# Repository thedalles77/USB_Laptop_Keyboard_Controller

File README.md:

# USB_Laptop_Keyboard_Controller
 This repo contains all the files that are needed to make a USB keyboard/touchpad controller as well as a KVM from an old laptop.

 See the USB keyboard video at https://vimeo.com/458595950 and the updated video at https://vimeo.com/888367797?share=copy
 
 See the keyboard Instructable at https://www.instructables.com/id/How-to-Make-a-USB-Laptop-Keyboard-Controller/

 Instead of the manual method to create the key matrix, use Marcel's Python program which I've forked and updated so it will work with the Teensy 4.0, 4.1, and 2.0++. 
 
 The updated Python code is here:
 
 https://github.com/thedalles77/USB_Laptop_Keyboard_Controller-1/blob/master/matrixgenerator.py
 
 See the KVM Instructable at https://www.instructables.com/DIY-Portable-KVM-Crashcart-From-Recycled-Laptop-Pr/ 

 If you don't know how to solder but still want to build a USB laptop keyboard, check out the "No_solder_method" PDF file at https://github.com/thedalles77/USB_Laptop_Keyboard_Controller/blob/master/Keyboard_Scanner_Eagle_Layouts/No_solder_method.pdf.

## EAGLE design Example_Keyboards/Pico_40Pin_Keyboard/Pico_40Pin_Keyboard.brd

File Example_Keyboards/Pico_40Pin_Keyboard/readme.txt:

This project is in development.

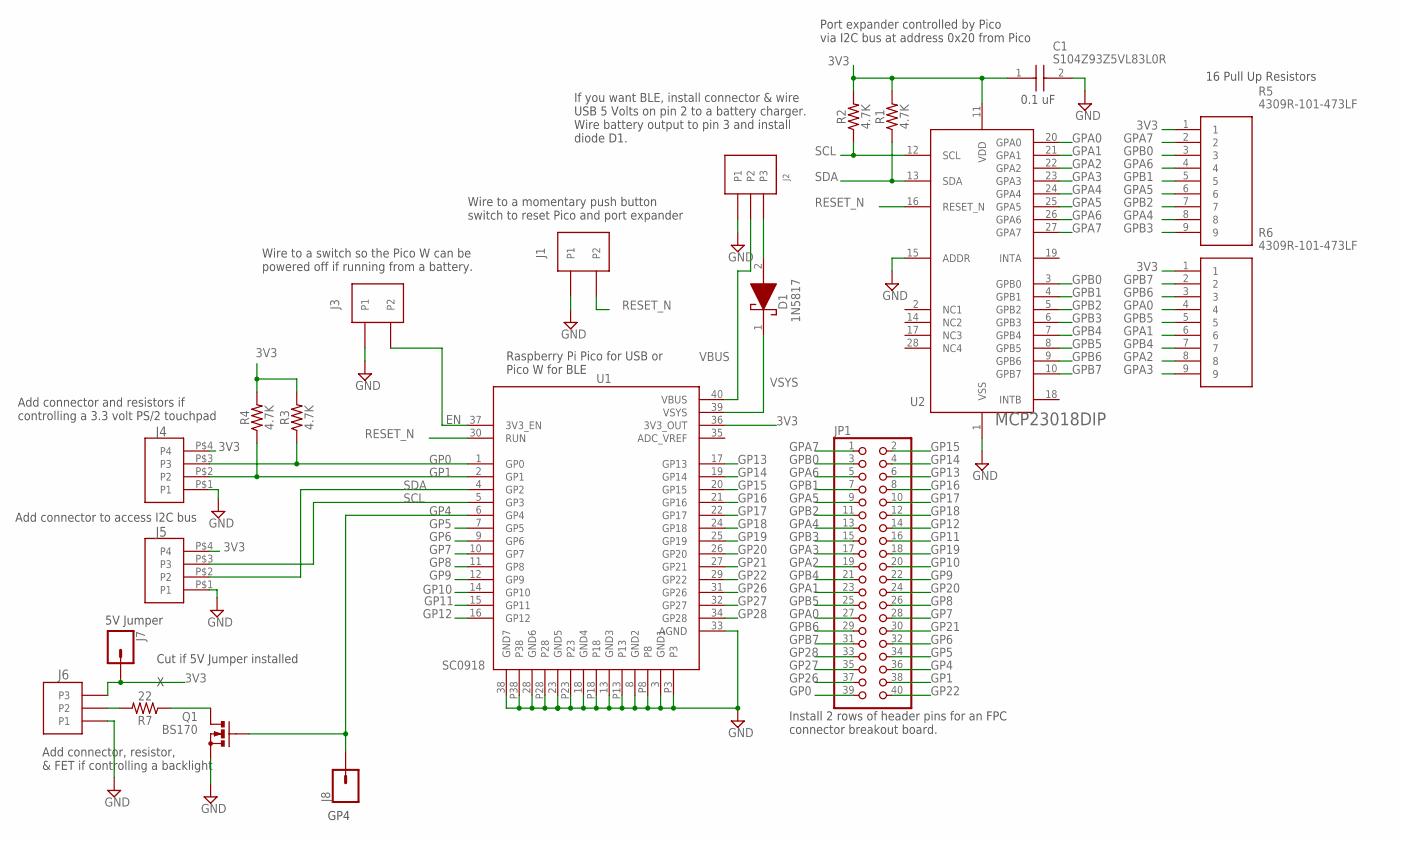
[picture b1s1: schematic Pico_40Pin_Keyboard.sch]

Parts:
C1: S104Z93Z5VL83L0R
D1: 1N5817; DIOAD1410W86L470D235
J1, J3: JST-PH-2PIN
J2, J6: JST-PH-3PIN
J4, J5: JST-PH-4PIN
J7, J8: CONN_01; 1X01
JP1: PINHD-2X20; 2X20
Q1: BS170; SOT54E
R1, R2, R3, R4: 4.7K; AXIAL-0.3
R5, R6: 4309R-101-473LF
R7: 22; AXIAL-0.3
U1: SC0918; MODULE_SC0918
U2: MCP23018DIP

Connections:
3V3: C1.1, J4.P$4 (P4), J5.P$4 (P4), J6.P$3 (P3), J7.1, R1.P$2 (2), R2.P$2 (2), R3.P$2 (2), R4.P$2 (2), R5.1, R6.1, U1.36 (3V3_OUT), U2.11 (VDD)
ADC_VREF: U1.35 (ADC_VREF)
EN: J3.P$2 (P2), U1.37 (3V3_EN)
GND: C1.2, J1.P$1 (P1), J2.P$1 (P1), J3.P$1 (P1), J4.P$1 (P1), J5.P$1 (P1), J6.P$1 (P1), Q1.S, U1.3 (GND1), U1.8 (GND2), U1.13 (GND3), U1.18 (GND4), U1.23 (GND5), U1.28 (GND6), U1.33 (AGND), U1.38 (GND7), U1.P3, U1.P8, U1.P13, U1.P18, U1.P23, U1.P28, U1.P38, U2.1 (VSS), U2.15 (ADDR)
GP0: J4.P$3 (P3), JP1.39, R3.P$1 (1), U1.1 (GP0)
GP1: J4.P$2 (P2), JP1.38, R4.P$1 (1), U1.2 (GP1)
GP4: J8.1, JP1.36, Q1.G, U1.6 (GP4)
GP5: JP1.34, U1.7 (GP5)
GP6: JP1.32, U1.9 (GP6)
GP7: JP1.28, U1.10 (GP7)
GP8: JP1.26, U1.11 (GP8)
GP9: JP1.22, U1.12 (GP9)
GP10: JP1.20, U1.14 (GP10)
GP11: JP1.16, U1.15 (GP11)
GP12: JP1.14, U1.16 (GP12)
GP13: JP1.6, U1.17 (GP13)
GP14: JP1.4, U1.19 (GP14)
GP15: JP1.2, U1.20 (GP15)
GP16: JP1.8, U1.21 (GP16)
GP17: JP1.10, U1.22 (GP17)
GP18: JP1.12, U1.24 (GP18)
GP19: JP1.18, U1.25 (GP19)
GP20: JP1.24, U1.26 (GP20)
GP21: JP1.30, U1.27 (GP21)
GP22: JP1.40, U1.29 (GP22)
GP26: JP1.37, U1.31 (GP26)
GP27: JP1.35, U1.32 (GP27)
GP28: JP1.33, U1.34 (GP28)
GPA0: JP1.27, R6.4, U2.20 (GPA0)
GPA1: JP1.23, R6.6, U2.21 (GPA1)
GPA2: JP1.19, R6.8, U2.22 (GPA2)
GPA3: JP1.17, R6.9, U2.23 (GPA3)
GPA4: JP1.13, R5.8, U2.24 (GPA4)
GPA5: JP1.9, R5.6, U2.25 (GPA5)
GPA6: JP1.5, R5.4, U2.26 (GPA6)
GPA7: JP1.1, R5.2, U2.27 (GPA7)
GPB0: JP1.3, R5.3, U2.3 (GPB0)
GPB1: JP1.7, R5.5, U2.4 (GPB1)
GPB2: JP1.11, R5.7, U2.5 (GPB2)
GPB3: JP1.15, R5.9, U2.6 (GPB3)
GPB4: JP1.21, R6.7, U2.7 (GPB4)
GPB5: JP1.25, R6.5, U2.8 (GPB5)
GPB6: JP1.29, R6.3, U2.9 (GPB6)
GPB7: JP1.31, R6.2, U2.10 (GPB7)
unnamed: J6.P$2 (P2), R7.P$2 (2)
unnamed: Q1.D, R7.P$1 (1)
RESET_N: J1.P$2 (P2), U1.30 (RUN), U2.16 (RESET_N)
SCL: J5.P$3 (P3), R2.P$1 (1), U1.5 (GP3), U2.12 (SCL)
SDA: J5.P$2 (P2), R1.P$1 (1), U1.4 (GP2), U2.13 (SDA)
VBAT: D1.2 (A), J2.P$3 (P3)
VBUS: J2.P$2 (P2), U1.40 (VBUS)
VSYS: D1.1 (K), U1.39 (VSYS)

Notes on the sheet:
If you want BLE, install connector & wire USB 5 Volts on pin 2 to a battery charger. Wire battery output to pin 3 and install diode D1.
Wire to a momentary push button switch to reset Pico and port expander
Wire to a switch so the Pico W can be powered off if running from a battery.
Install 2 rows of header pins for an FPC connector breakout board.
0.1 uF
Raspberry Pi Pico for USB or Pico W for BLE
Add connector and resistors if controlling a 3.3 volt PS/2 touchpad
Add connector to access I2C bus
Port expander controlled by Pico via I2C bus at address 0x20 from Pico
16 Pull Up Resistors
Cut if 5V Jumper installed
5V Jumper
GP4
Add connector, resistor, & FET if controlling a backlight

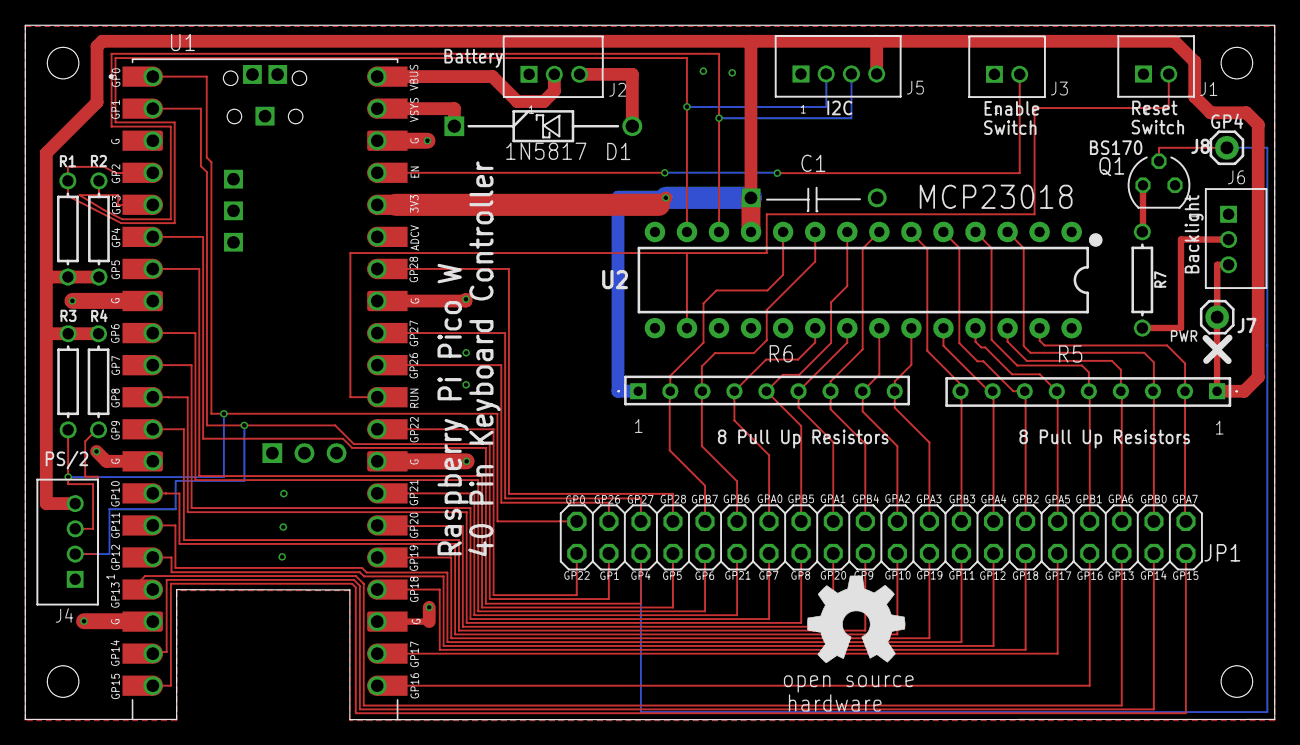
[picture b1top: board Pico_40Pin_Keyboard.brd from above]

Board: 2 copper layers, 99.0 x 55.0 mm, 23 parts (0 on the bottom side), 51 nets.

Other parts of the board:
U$1, U$2: OSHW_8MM

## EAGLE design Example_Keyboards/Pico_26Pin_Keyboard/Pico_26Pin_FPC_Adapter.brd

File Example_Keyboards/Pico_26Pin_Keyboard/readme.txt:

Laptop Keyboard with up to 26 pins on its FPC cable is Controlled with a Raspberry Pi Pico for USB operation.

See the PDF and step 16 of my Instructable for more information

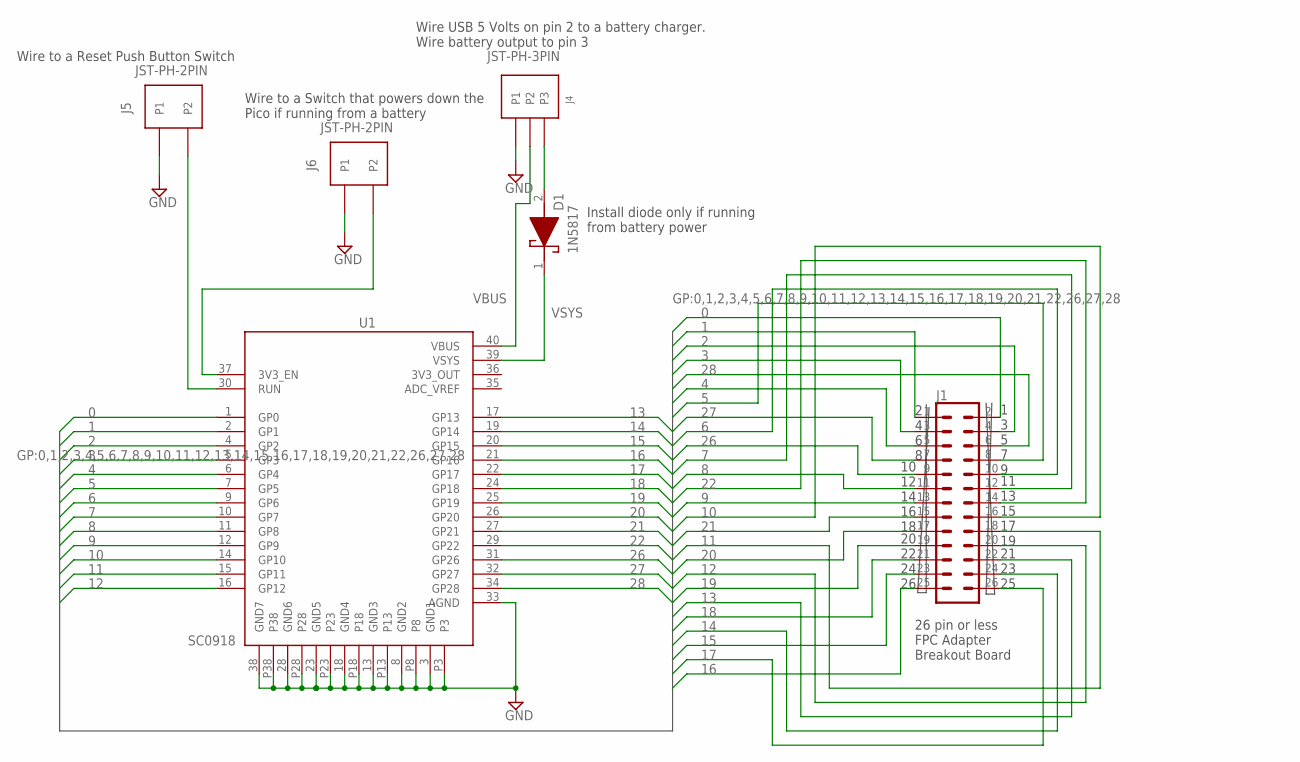
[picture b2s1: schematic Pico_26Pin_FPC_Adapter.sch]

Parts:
D1: 1N5817; DIOAD1410W86L470D235
J1: CONN_13X22X13; 2X13
J4: JST-PH-3PIN
J5, J6: JST-PH-2PIN
U1: SC0918; MODULE_SC0918

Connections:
0: J1.2, U1.1 (GP0)
1: J1.1, U1.2 (GP1)
2: J1.4, U1.4 (GP2)
3: J1.3, U1.5 (GP3)
3V3_OUT: U1.36 (3V3_OUT)
4: J1.5, U1.6 (GP4)
5: J1.8, U1.7 (GP5)
6: J1.10, U1.9 (GP6)
7: J1.12, U1.10 (GP7)
8: J1.11, U1.11 (GP8)
9: J1.13, U1.12 (GP9)
10: J1.16, U1.14 (GP10)
11: J1.18, U1.15 (GP11)
12: J1.20, U1.16 (GP12)
13: J1.22, U1.17 (GP13)
14: J1.24, U1.19 (GP14)
15: J1.23, U1.20 (GP15)
16: J1.25, U1.21 (GP16)
17: J1.26, U1.22 (GP17)
18: J1.21, U1.24 (GP18)
19: J1.19, U1.25 (GP19)
20: J1.17, U1.26 (GP20)
21: J1.15, U1.27 (GP21)
22: J1.14, U1.29 (GP22)
26: J1.9, U1.31 (GP26)
27: J1.7, U1.32 (GP27)
28: J1.6, U1.34 (GP28)
ADC_VREF: U1.35 (ADC_VREF)
GND: J4.P$1 (P1), J5.P$1 (P1), J6.P$1 (P1), U1.3 (GND1), U1.8 (GND2), U1.13 (GND3), U1.18 (GND4), U1.23 (GND5), U1.28 (GND6), U1.33 (AGND), U1.38 (GND7), U1.P3, U1.P8, U1.P13, U1.P18, U1.P23, U1.P28, U1.P38
unnamed: J5.P$2 (P2), U1.30 (RUN)
unnamed: J6.P$2 (P2), U1.37 (3V3_EN)
VBAT: D1.2 (A), J4.P$3 (P3)
VBUS: J4.P$2 (P2), U1.40 (VBUS)
VSYS: D1.1 (K), U1.39 (VSYS)

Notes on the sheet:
Wire USB 5 Volts on pin 2 to a battery charger. Wire battery output to pin 3
Wire to a Reset Push Button Switch
Wire to a Switch that powers down the Pico if running from a battery
Install diode only if running from battery power
26 pin or less FPC Adapter Breakout Board
1 3 5 7 9
11 13 15 17 19
21 23 25
2 4 6 8
10 12 14 16 18
20 22 24 26

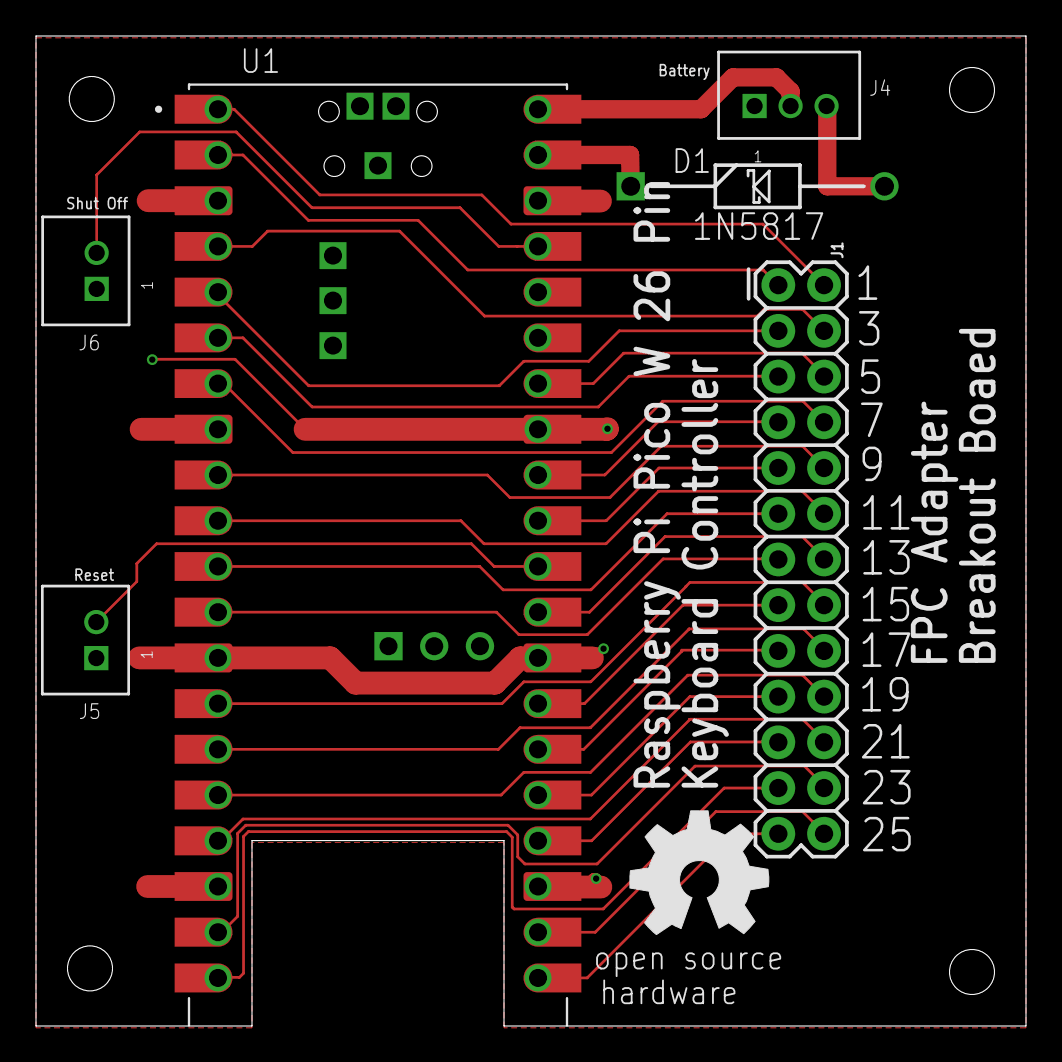
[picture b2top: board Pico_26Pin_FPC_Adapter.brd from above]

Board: 2 copper layers, 55.0 x 55.0 mm, 8 parts (0 on the bottom side), 32 nets.

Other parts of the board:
U$1, U$2: OSHW_8MM

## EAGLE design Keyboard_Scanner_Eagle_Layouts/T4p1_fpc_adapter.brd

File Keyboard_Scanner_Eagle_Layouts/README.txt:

The Eagle .brd files can be sent to OSHPark. The Zipped gerber files can be sent to JLCPCB for fabrication.

The files in this folder are for creating a "generic" FPC connector board. For keyboards with special connectors, look in the Example_Keyboards folder.

If you want to build a prototype keyboard controller without soldering a board, read the PDF file titled "No_solder_method".

The Teensy 4.0, 4.1, and 2.0++ clone are available for purchase.

Teensy 4.0 board, schematic, and zipped Gerber files are called T4p0 and T4p0_cutout. They accept 1mm, 0.8mm, and 0.5mm surface mount FPC connectors.

Teensy 4.1 board, schematic, and zipped Gerber files are called T4p1 and T4p1_cutout. They accept 1mm, 0.8mm, and 0.5mm surface mount FPC connectors.

The T4p1_thruhole board, schematic, and zipped Gerber files are for 1mm or 1.25mm pitch thru hole connectors. 

The Teensy 2.0++ (clone) uses the Keyboard_Scanner_2pp_RevA board, schematic, and zipped Gerber files. This board avoids using the I/O pin tied to the LED. 

The following are useful FPC breakout boards:

FPC_8pin1mm.brd EagleCad file for 8 pin 1mm breakout board

FPC_10pin0p5mm.brd  EagleCad file for 10 pin 0.5mm breakout board

FPC_18pin1mm.brd  EagleCad file for 18 pin 1mm, 0.8mm, or 0.5mm breakout board

The following boards use the Teensy LC and 3.2 which are obsolete and should not be used for new designs. Use the Teensy 4.0, 4.1, and 2.0++ (clone) for new designs.

Keyboard_Scanner.brd EagleCad circuit board file for Teensy LC or 3.2. Original layout shown in the video. The LT2 board is better.

Keyboard_Scanner_LT.brd EagleCad file same as above with 2 bit Level Translator for touchpad Clock and Data on Teensy LC side. The LT2 board is better.

Keyboard_Scanner_LT2.brd EagleCad file same as above with improved hole spacing for using right angle header on Teensy 3.2 backside signals

Keyboard_Scanner_LT_0p5.brd EagleCad file same as above except made for a 0.5mm pitch FPC connector

Keyboard_Scanner_Dual.brd EagleCad file is for keyboards with dual FPC cables but it uses the obsolete Teensy LC and 3.2

Keyboard_Scanner_4p0.brd EagleCad file for Teensy LC or 4.0 with 1mm or 0.8mm pitch. The T4p0.brd is better

Keyboard_Scanner_4p0_0p5.brd EagleCad file for Teensy LC or 4.0 with 1mm or 0.5mm pitch. The T4p0.brd is better

Keyboard_Scanner_LC_thruhole.brd EagleCad file for thru-hole 1mm pitch FPC cables with up to 26 pins. The T4p1_thruhole.brd is better

TeensyLC_1p25.brd EagleCad file for thru-hole 1.25mm pitch FPC cables with up to 26 pins. The T4p1_thruhole.brd is better

Keyboard_Scanner_2pp.brd EagleCad file for Teensy ++2.0. The Keyboard_Scanner_2pp_RevA.brd is better

Teensy3p2Cutout.brd EagleCad file has a cutout for a Teensy 3.2. The T4p0_cutout.brd is better.

Teensy3p2CutoutFlip.brd EagleCad file is the same as above file but it has the cutout on the right side instead of the left side.

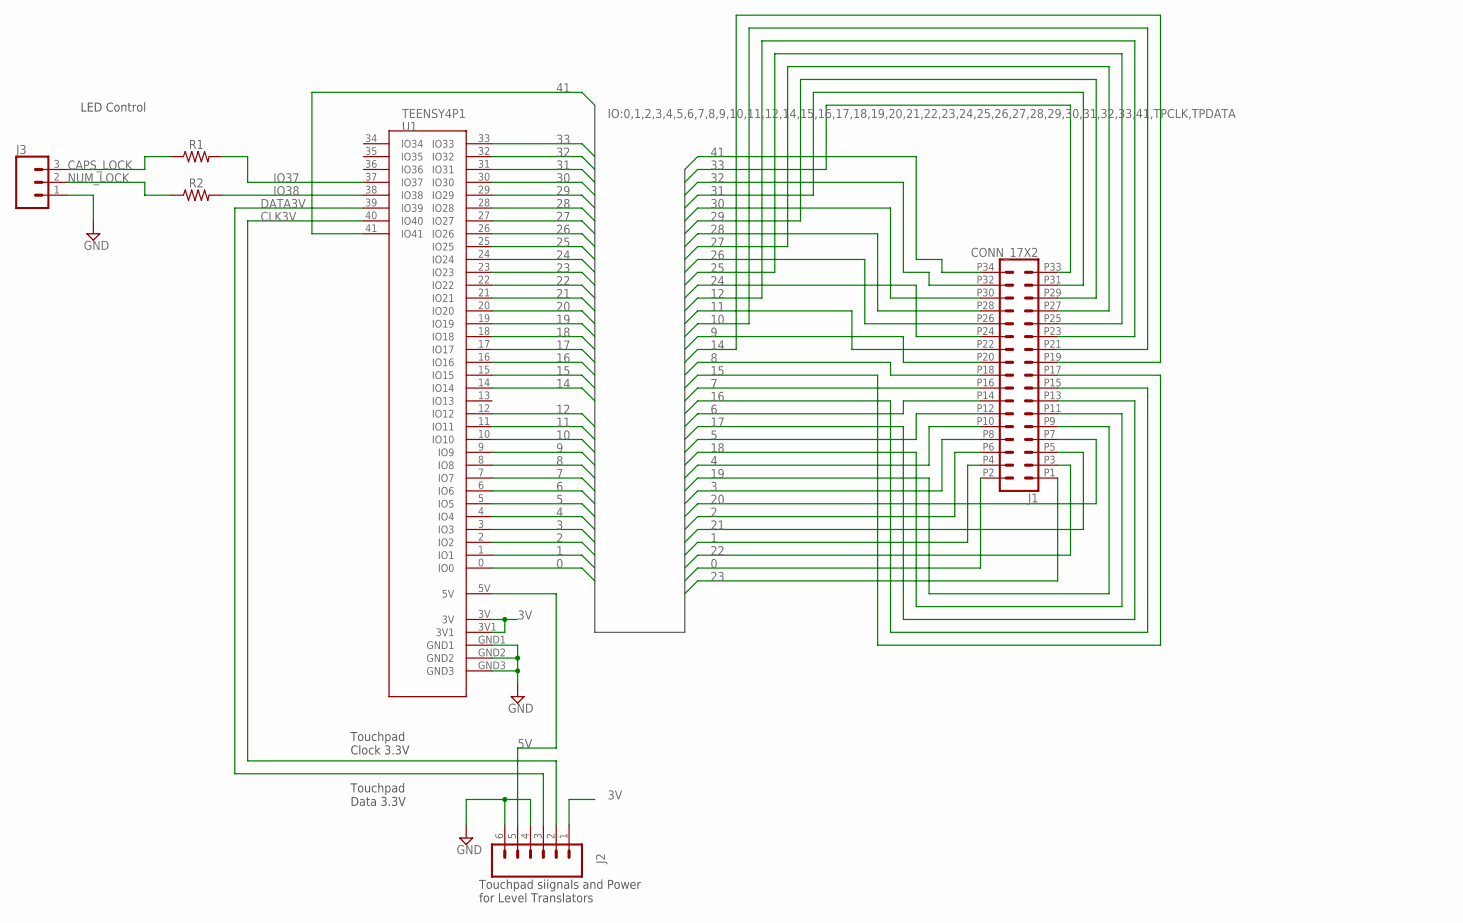
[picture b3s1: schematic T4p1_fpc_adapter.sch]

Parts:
J1: CONN_17X2; 2X17
J2: CONN_06NO_SILK_FEMALE_PTH; 1X06_NO_SILK
J3: CONN_031X03_NO_SILK; 1X03_NO_SILK
R1, R2: RESISTOR_AXIAL; AXIAL-0.3
U1: TEENSY4P1

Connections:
0: J1.P2 (2), U1.0 (IO0)
1: J1.P4 (4), U1.1 (IO1)
2: J1.P6 (6), U1.2 (IO2)
3: J1.P8 (8), U1.3 (IO3)
3V: J2.1, U1.3V, U1.3V1
4: J1.P10 (10), U1.4 (IO4)
5: J1.P12 (12), U1.5 (IO5)
5V: J2.5, U1.5V
6: J1.P14 (14), U1.6 (IO6)
7: J1.P16 (16), U1.7 (IO7)
8: J1.P18 (18), U1.8 (IO8)
9: J1.P20 (20), U1.9 (IO9)
10: J1.P21 (21), U1.10 (IO10)
11: J1.P22 (22), U1.11 (IO11)
12: J1.P23 (23), U1.12 (IO12)
14: J1.P19 (19), U1.14 (IO14)
15: J1.P17 (17), U1.15 (IO15)
16: J1.P15 (15), U1.16 (IO16)
17: J1.P13 (13), U1.17 (IO17)
18: J1.P11 (11), U1.18 (IO18)
19: J1.P9 (9), U1.19 (IO19)
20: J1.P7 (7), U1.20 (IO20)
21: J1.P5 (5), U1.21 (IO21)
22: J1.P3 (3), U1.22 (IO22)
23: J1.P1 (1), U1.23 (IO23)
24: J1.P24 (24), U1.24 (IO24)
25: J1.P25 (25), U1.25 (IO25)
26: J1.P26 (26), U1.26 (IO26)
27: J1.P27 (27), U1.27 (IO27)
28: J1.P28 (28), U1.28 (IO28)
29: J1.P29 (29), U1.29 (IO29)
30: J1.P30 (30), U1.30 (IO30)
31: J1.P31 (31), U1.31 (IO31)
32: J1.P32 (32), U1.32 (IO32)
33: J1.P33 (33), U1.33 (IO33)
41: J1.P34 (34), U1.41 (IO41)
CAPS_LOCK: J3.3, R1.P$1 (1)
CLK3V: J2.2, U1.40 (IO40)
DATA3V: J2.3, U1.39 (IO39)
GND: J2.4, J2.6, J3.1, U1.GND1, U1.GND2, U1.GND3
IO37: R1.P$2 (2), U1.37 (IO37)
IO38: R2.P$2 (2), U1.38 (IO38)
NUM_LOCK: J3.2, R2.P$1 (1)

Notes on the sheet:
Touchpad siignals and Power for Level Translators
Touchpad Clock 3.3V
Touchpad Data 3.3V
LED Control

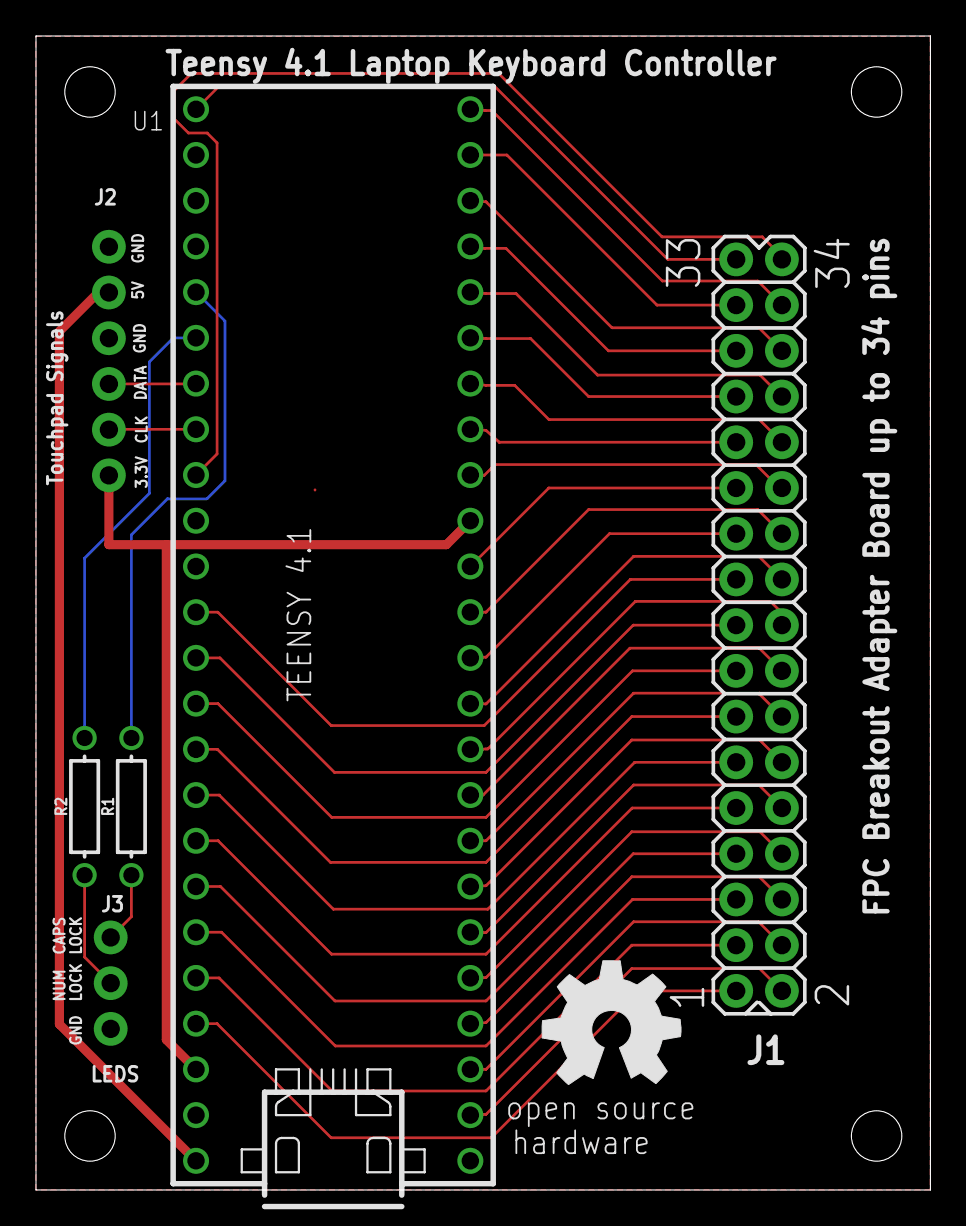
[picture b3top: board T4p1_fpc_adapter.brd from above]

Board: 2 copper layers, 49.7 x 64.1 mm, 8 parts (0 on the bottom side), 43 nets.

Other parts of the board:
U$1, U$2: OSHW_8MM

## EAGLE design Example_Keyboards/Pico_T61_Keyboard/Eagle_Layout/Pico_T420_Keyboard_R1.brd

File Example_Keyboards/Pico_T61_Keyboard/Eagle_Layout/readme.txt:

The ZIP file is the Eagle .BRD file converted to GERBER format for sending to board houses like JLCPCB.

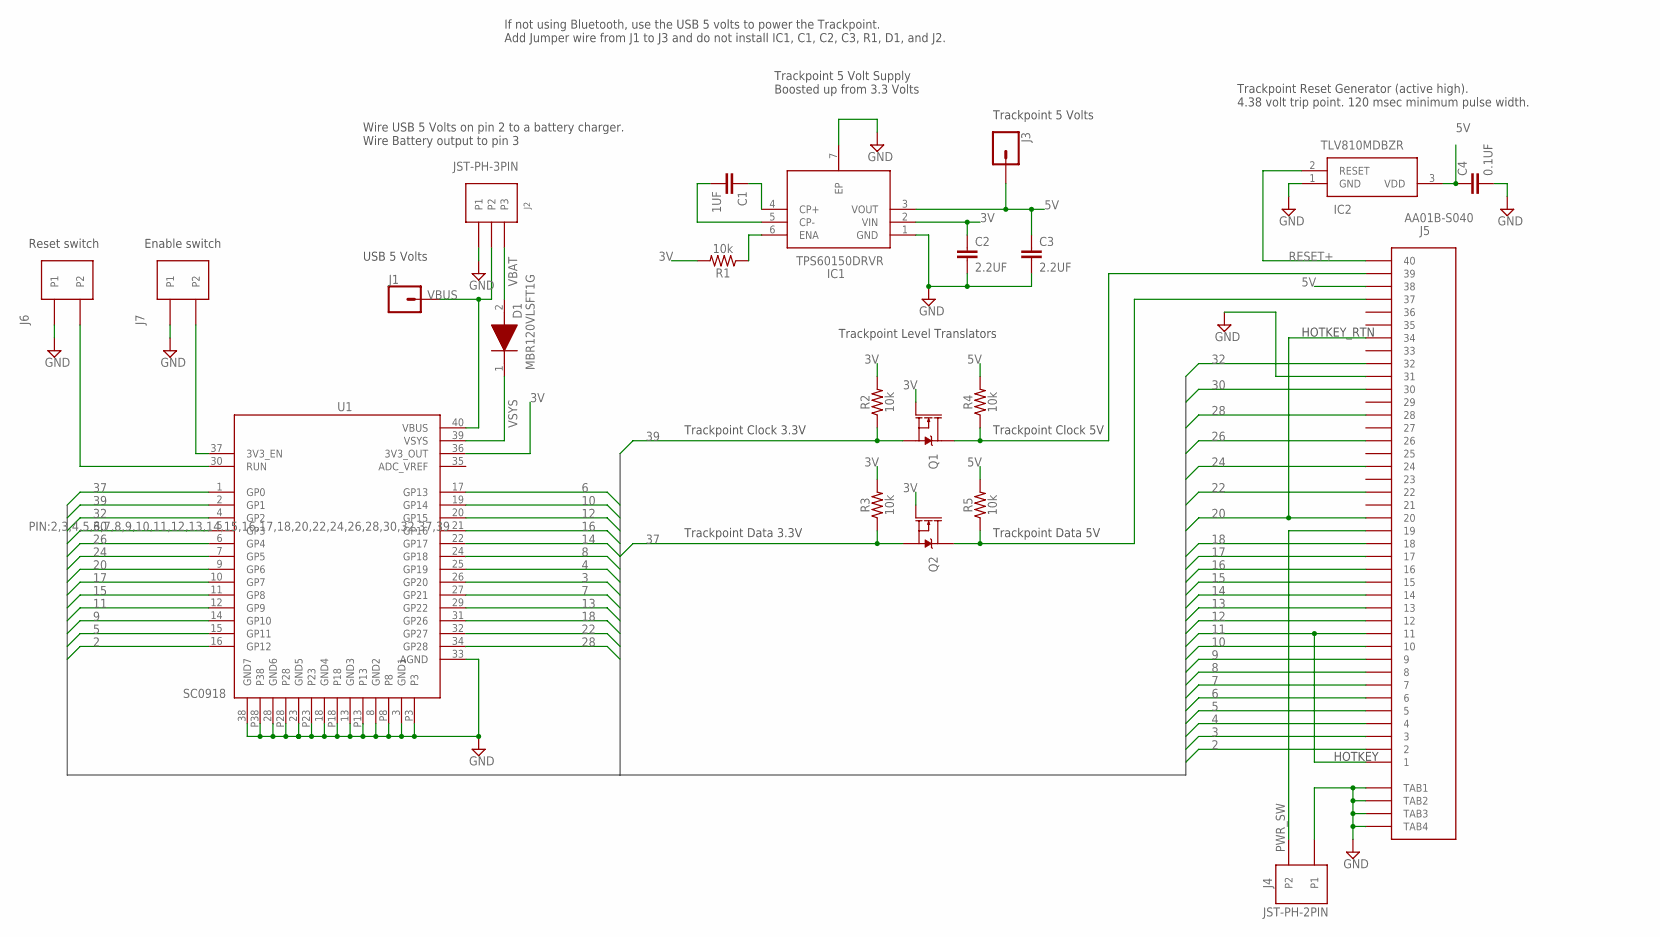
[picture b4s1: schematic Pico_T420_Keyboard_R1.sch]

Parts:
C1: 1UF; 0603_CAP
C2, C3: 2.2UF; 0603_CAP
C4: 0.1UF; 0603_CAP
D1: MBR120VLSFT1G; SODFL3616X98N
IC1: TPS60150DRVR; SON65P200X200X80-7N
IC2: TLV810MDBZR; SOT95P237X112-3N
J1, J3: CONN_01; 1X01
J2: JST-PH-3PIN
J4, J6, J7: JST-PH-2PIN
J5: AA01B-S040; WM6787_AA01B
Q1, Q2: 220mA/50V/3.5Ω; SOT23-3
R1, R2, R3, R4, R5: 10k; 0603
U1: SC0918; MODULE_SC0918

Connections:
2: J5.P$2 (2), U1.16 (GP12)
3: J5.P$3 (3), U1.26 (GP20)
3V: C2.1, IC1.2 (VIN), Q1.1 (G), Q2.1 (G), R1.2, R2.2, R3.2, U1.36 (3V3_OUT)
4: J5.P$4 (4), U1.25 (GP19)
5: J5.P$5 (5), U1.15 (GP11)
5V: C3.1, C4.1, IC1.3 (VOUT), IC2.3 (VDD), J3.1, J5.P$38 (38), R4.2, R5.2
6: J5.P$6 (6), U1.17 (GP13)
7: J5.P$7 (7), U1.27 (GP21)
8: J5.P$8 (8), U1.24 (GP18)
9: J5.P$9 (9), U1.14 (GP10)
10: J5.P$10 (10), U1.19 (GP14)
11: J5.P$1 (1), J5.P$11 (11), U1.12 (GP9)
12: J5.P$12 (12), U1.20 (GP15)
13: J5.P$13 (13), U1.29 (GP22)
14: J5.P$14 (14), U1.22 (GP17)
15: J5.P$15 (15), U1.11 (GP8)
16: J5.P$16 (16), U1.21 (GP16)
17: J5.P$17 (17), U1.10 (GP7)
18: J5.P$18 (18), U1.31 (GP26)
20: J5.P$20 (20), J5.P$34 (34), U1.9 (GP6)
22: J5.P$22 (22), U1.32 (GP27)
24: J5.P$24 (24), U1.7 (GP5)
26: J5.P$26 (26), U1.6 (GP4)
28: J5.P$28 (28), U1.34 (GP28)
30: J5.P$30 (30), U1.5 (GP3)
32: J5.P$32 (32), U1.4 (GP2)
37: Q2.2 (S), R3.1, U1.1 (GP0)
39: Q1.2 (S), R2.1, U1.2 (GP1)
ADC_VREF: U1.35 (ADC_VREF)
GND: C2.2, C3.2, C4.2, IC1.1 (GND), IC1.7 (EP), IC2.1 (GND), J2.P$1 (P1), J4.P$1 (P1), J5.P$31 (31), J5.TAB1, J5.TAB2, J5.TAB3, J5.TAB4, J6.P$1 (P1), J7.P$1 (P1), U1.3 (GND1), U1.8 (GND2), U1.13 (GND3), U1.18 (GND4), U1.23 (GND5), U1.28 (GND6), U1.33 (AGND), U1.38 (GND7), U1.P3, U1.P8, U1.P13, U1.P18, U1.P23, U1.P28, U1.P38
unnamed: J6.P$2 (P2), U1.30 (RUN)
unnamed: C1.1, IC1.4 (CP+)
unnamed: C1.2, IC1.5 (CP-)
unnamed: J7.P$2 (P2), U1.37 (3V3_EN)
unnamed: IC1.6 (ENA), R1.1
PWR_SW: J4.P$2 (P2), J5.P$19 (19)
RESET+: IC2.2 (RESET), J5.P$40 (40)
TP_CLK: J5.P$39 (39), Q1.3 (D), R4.1
TP_DATA: J5.P$37 (37), Q2.3 (D), R5.1
VBAT: D1.2 (A), J2.P$3 (P3)
VBUS: J1.1, J2.P$2 (P2), U1.40 (VBUS)
VSYS: D1.1 (K), U1.39 (VSYS)

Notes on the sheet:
Trackpoint Clock 3.3V
Trackpoint Data 3.3V
Trackpoint Clock 5V
Trackpoint Data 5V
Trackpoint Level Translators
HOTKEY
HOTKEY_RTN
Trackpoint 5 Volt Supply Boosted up from 3.3 Volts
Trackpoint Reset Generator (active high). 4.38 volt trip point. 120 msec minimum pulse width.
Wire USB 5 Volts on pin 2 to a battery charger. Wire Battery output to pin 3
USB 5 Volts
Trackpoint 5 Volts
If not using Bluetooth, use the USB 5 volts to power the Trackpoint. Add Jumper wire from J1 to J3 and do not install IC1, C1, C2, C3, R1, D1, and J2.
Reset switch
Enable switch

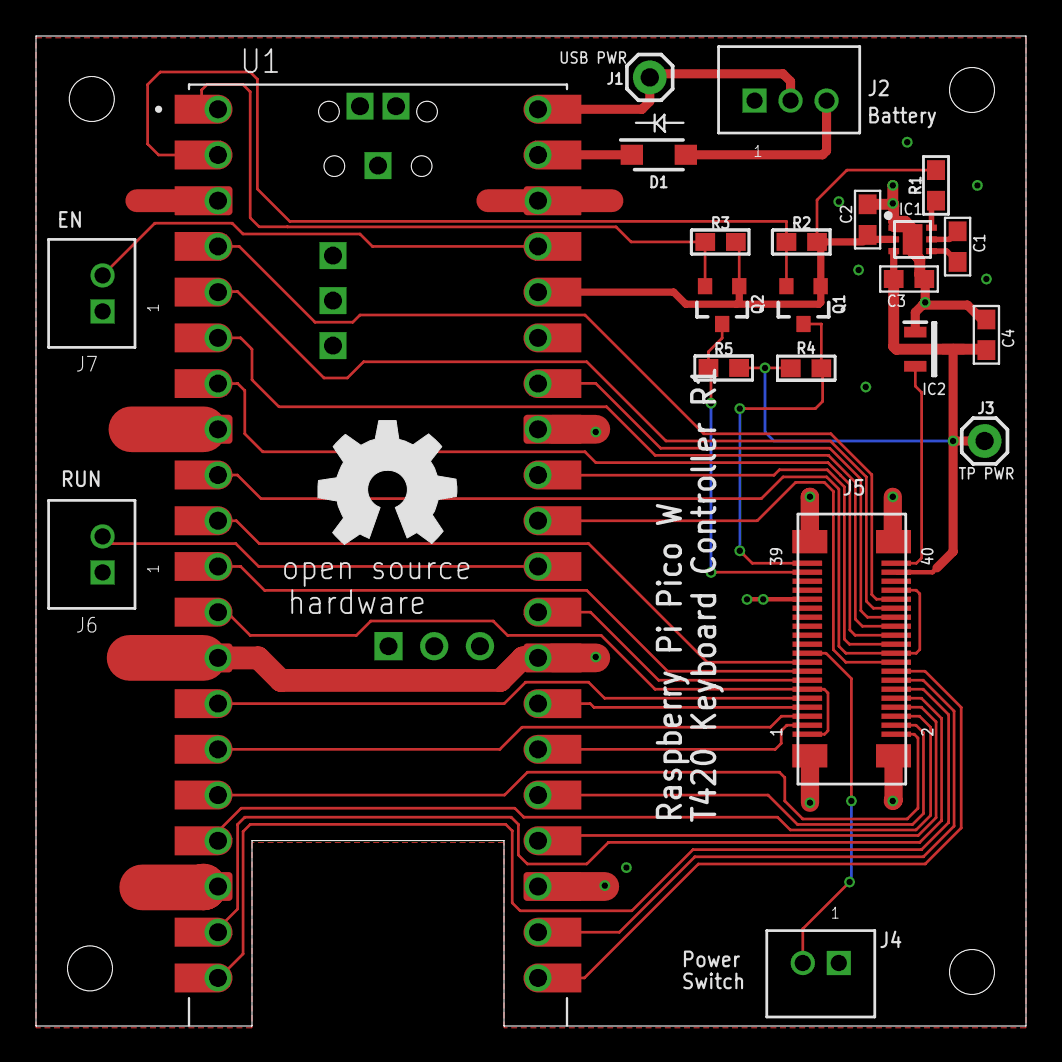
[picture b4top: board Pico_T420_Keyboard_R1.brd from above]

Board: 2 copper layers, 55.0 x 55.0 mm, 24 parts (0 on the bottom side), 41 nets.

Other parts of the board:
U$1, U$2: OSHW_8MM

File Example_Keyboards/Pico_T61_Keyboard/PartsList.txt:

Partlist for Pico_T61_Keyboard

Qty Value          Device                 Package             Parts              Description                                                                                                                                         
2   None           CONN_01PTH_NO_SILK_KIT 1X01NS_KIT          J1, J3             Single connection point for jumper wire.                           
1   0.1UF          0603_CAP               0603_CAP            C4                 Bypass cap for reset generator IC                                       
5   10k            10KOHM-0603-1/10W-1%   0603                R1, R2, R3, R4, R5 10KΩ 0603 size resistor                                                 
1   1UF            0603_CAP               0603_CAP            C1                 1uF X7R 0603 size capacitor                                             
2   2.2UF          0603_CAP               0603_CAP            C2, C3             2.2uF X7R 0603 size capacitor                                           
2   220mA/50V/3.5Ω MOSFET-NCH-BSS138      SOT23-3             Q1, Q2             BSS138 N-channel MOSFET                                                 
1   AA01B-S040     AA01B-S040             AA01B-S040          J5                 40 Pin Keyboard Connector                                               
1   JST-PH-2PIN    JST-PH-2PIN            JST-PH-2PIN         J4                 2 Pin JST Connector                                                     
1   JST-PH-3PIN    JST-PH-3PIN            JST-PH-3PIN         J2                 3 Pin JST Connector                                                     
1   MBR120VLSFT1G  MBR120VLSFT1G          SODFL3616X98N       D1                 Diode Schottky 20V 1A                     
1   SC0918         SC0918                 MODULE_SC0918       U1                 Raspberry Pi Pico W (with or without header pins)                       
1   TLV810MDBZR    TLV810MDBZR            SOT95P237X112-3N    IC2                3-pin Reset IC with active-high, push-pull output  
1   TPS60150DRVR   TPS60150DRVR           SON65P200X200X80-7N IC1                140mA, 5V Charge Pump

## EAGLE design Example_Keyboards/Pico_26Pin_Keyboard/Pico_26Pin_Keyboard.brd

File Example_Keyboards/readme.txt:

This folder contains keyboard code, documentation, and PDF's that detail how to make a USB keyboard controller from a laptop keyboard.

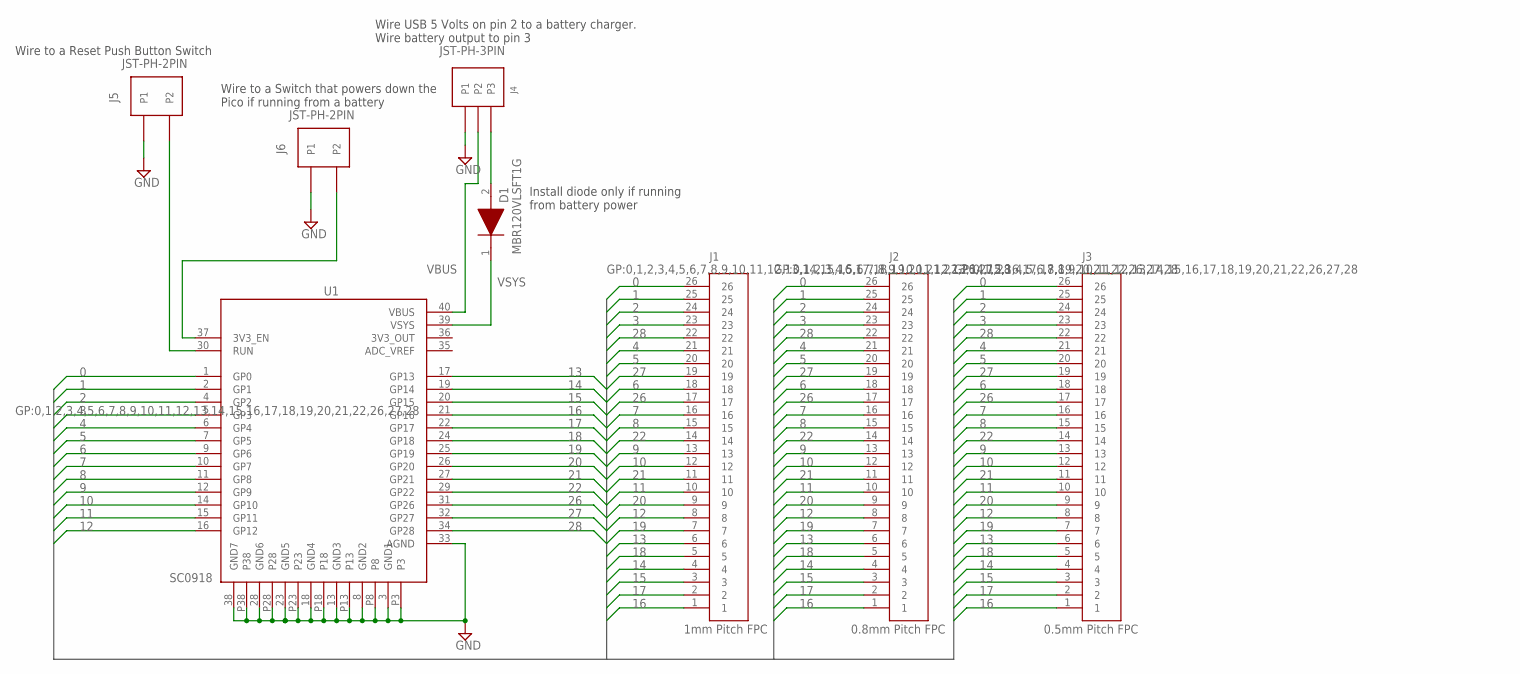
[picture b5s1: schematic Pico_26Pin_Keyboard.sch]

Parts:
D1: MBR120VLSFT1G; SODFL3616X98N
J1: 1mm Pitch FPC; FPC26
J2: 0.8mm Pitch FPC; FPC26_P8MM
J3: 0.5mm Pitch FPC; FPC26_P5MM
J4: JST-PH-3PIN
J5, J6: JST-PH-2PIN
U1: SC0918; MODULE_SC0918

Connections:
0: J1.26, J2.26, J3.26, U1.1 (GP0)
1: J1.25, J2.25, J3.25, U1.2 (GP1)
2: J1.24, J2.24, J3.24, U1.4 (GP2)
3: J1.23, J2.23, J3.23, U1.5 (GP3)
3V3_OUT: U1.36 (3V3_OUT)
4: J1.21, J2.21, J3.21, U1.6 (GP4)
5: J1.20, J2.20, J3.20, U1.7 (GP5)
6: J1.18, J2.18, J3.18, U1.9 (GP6)
7: J1.16, J2.16, J3.16, U1.10 (GP7)
8: J1.15, J2.15, J3.15, U1.11 (GP8)
9: J1.13, J2.13, J3.13, U1.12 (GP9)
10: J1.12, J2.12, J3.12, U1.14 (GP10)
11: J1.10, J2.10, J3.10, U1.15 (GP11)
12: J1.8, J2.8, J3.8, U1.16 (GP12)
13: J1.6, J2.6, J3.6, U1.17 (GP13)
14: J1.4, J2.4, J3.4, U1.19 (GP14)
15: J1.3, J2.3, J3.3, U1.20 (GP15)
16: J1.1, J2.1, J3.1, U1.21 (GP16)
17: J1.2, J2.2, J3.2, U1.22 (GP17)
18: J1.5, J2.5, J3.5, U1.24 (GP18)
19: J1.7, J2.7, J3.7, U1.25 (GP19)
20: J1.9, J2.9, J3.9, U1.26 (GP20)
21: J1.11, J2.11, J3.11, U1.27 (GP21)
22: J1.14, J2.14, J3.14, U1.29 (GP22)
26: J1.17, J2.17, J3.17, U1.31 (GP26)
27: J1.19, J2.19, J3.19, U1.32 (GP27)
28: J1.22, J2.22, J3.22, U1.34 (GP28)
ADC_VREF: U1.35 (ADC_VREF)
GND: J4.P$1 (P1), J5.P$1 (P1), J6.P$1 (P1), U1.3 (GND1), U1.8 (GND2), U1.13 (GND3), U1.18 (GND4), U1.23 (GND5), U1.28 (GND6), U1.33 (AGND), U1.38 (GND7), U1.P3, U1.P8, U1.P13, U1.P18, U1.P23, U1.P28, U1.P38
unnamed: J5.P$2 (P2), U1.30 (RUN)
unnamed: J6.P$2 (P2), U1.37 (3V3_EN)
VBAT: D1.2 (A), J4.P$3 (P3)
VBUS: J4.P$2 (P2), U1.40 (VBUS)
VSYS: D1.1 (K), U1.39 (VSYS)

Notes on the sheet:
Wire USB 5 Volts on pin 2 to a battery charger. Wire battery output to pin 3
Wire to a Reset Push Button Switch
Wire to a Switch that powers down the Pico if running from a battery
Install diode only if running from battery power

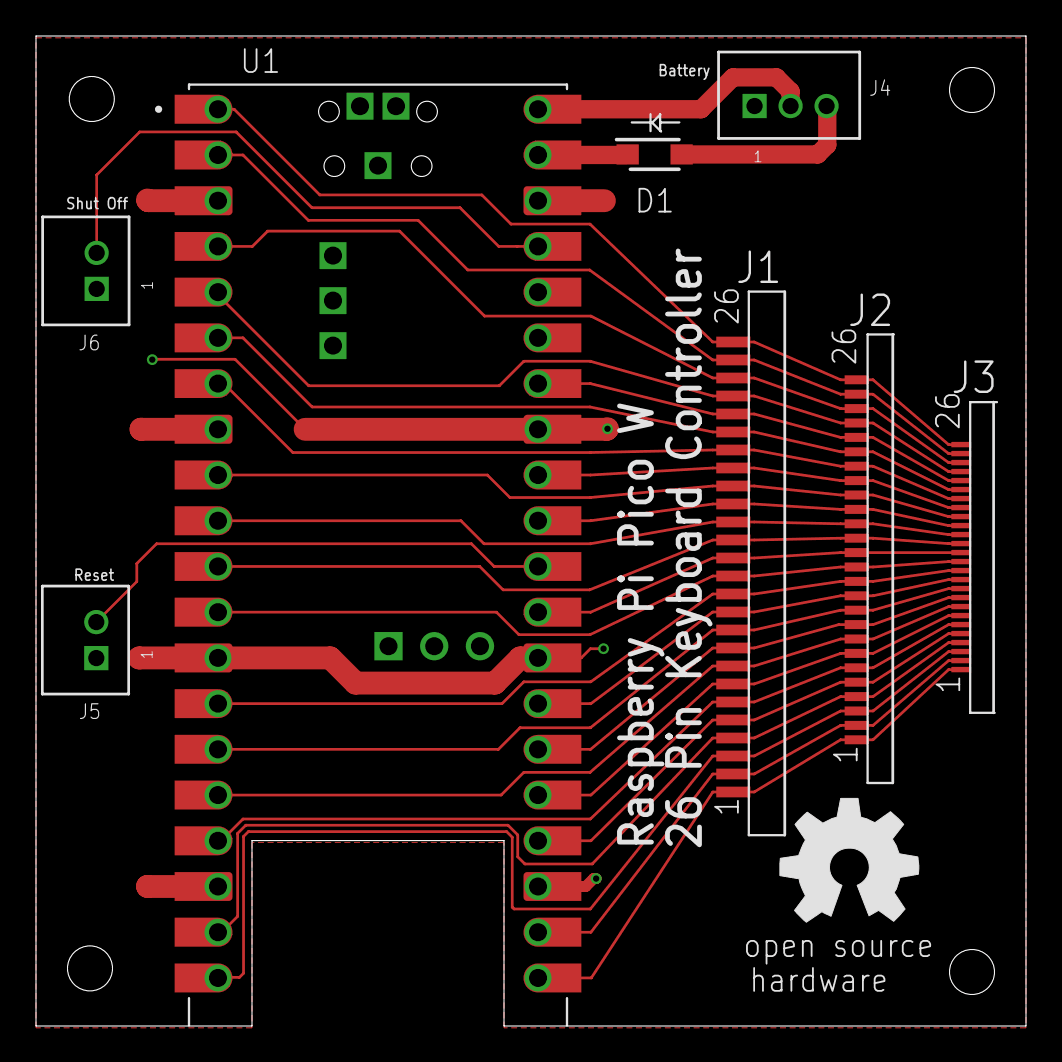
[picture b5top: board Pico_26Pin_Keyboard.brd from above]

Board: 2 copper layers, 55.0 x 55.0 mm, 10 parts (0 on the bottom side), 32 nets.

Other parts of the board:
U$1, U$2: OSHW_8MM

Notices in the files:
parts and their libraries:
SparkFun-Connectors: Licensing: Creative Commons ShareAlike 4.0 International - https://creativecommons.org/licenses/by-sa/4.0
